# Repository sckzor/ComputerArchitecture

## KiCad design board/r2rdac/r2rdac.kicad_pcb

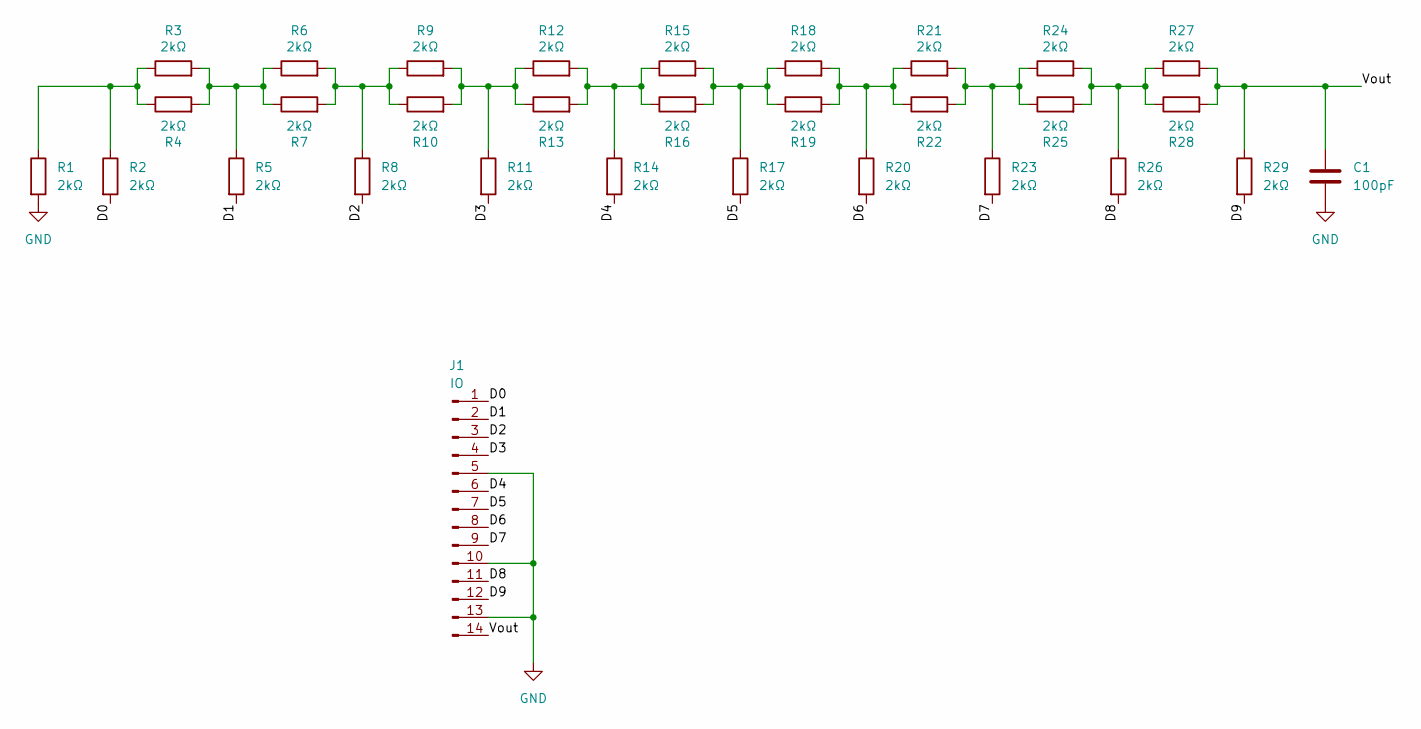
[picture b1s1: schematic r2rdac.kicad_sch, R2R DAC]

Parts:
C1: 100pF; C_0603_1608Metric
J1: IO; PinHeader_1x14_P2.54mm_Vertical
R1, R2, R3, R4, R5, R6, R7, R8, R9, R10, R11, R12, R13, R14, R15, R16, R17, R18, R19, R20, R21, R22, R23, R24, R25, R26, R27, R28, R29: 2kΩ; R_0603_1608Metric

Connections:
/D0: J1.1, R2.2
/D1: J1.2, R5.2
/D2: J1.3, R8.2
/D3: J1.4, R11.2
/D4: J1.6, R14.2
/D5: J1.7, R17.2
/D6: J1.8, R20.2
/D7: J1.9, R23.2
/D8: J1.11, R26.2
/D9: J1.12, R29.2
/Vout: C1.1, J1.14, R27.2, R28.2, R29.1
GND: C1.2, J1.5, J1.10, J1.13, R1.2
unnamed: R1.1, R2.1, R3.1, R4.1
unnamed: R3.2, R4.2, R5.1, R6.1, R7.1
unnamed: R6.2, R7.2, R8.1, R9.1, R10.1
unnamed: R9.2, R10.2, R11.1, R12.1, R13.1
unnamed: R12.2, R13.2, R14.1, R15.1, R16.1
unnamed: R15.2, R16.2, R17.1, R18.1, R19.1
unnamed: R18.2, R19.2, R20.1, R21.1, R22.1
unnamed: R21.2, R22.2, R23.1, R24.1, R25.1
unnamed: R24.2, R25.2, R26.1, R27.1, R28.1

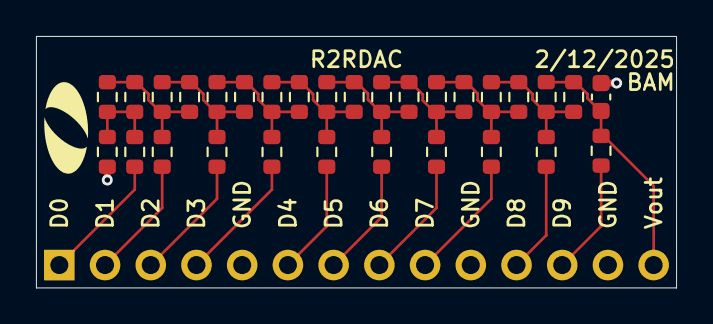
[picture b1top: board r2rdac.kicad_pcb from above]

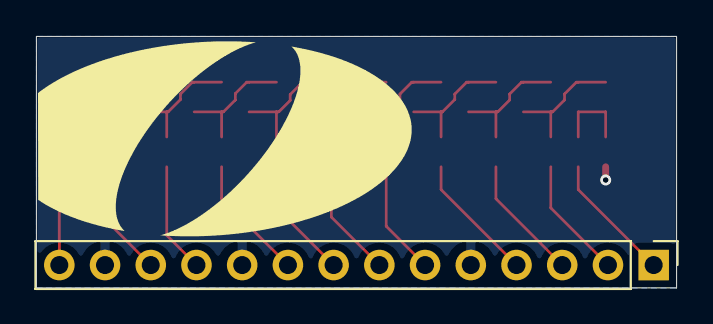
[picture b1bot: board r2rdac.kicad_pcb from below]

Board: 2 copper layers, 35.6 x 14.0 mm, 33 parts (2 on the bottom side), 21 nets.

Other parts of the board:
OlinLogoSm: G***; OlinLogoSm
svg2mod: G***; OlinLogoTruncated_0.4in

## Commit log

2025-09-22 Added all resources to the repository and my frist project assignment.
2025-09-22 Added video and changed file names
2025-09-30 Added all files for MP2
2025-09-30 added MP2 video
2025-10-03 Performed next code revision
2025-10-06 redid MP2
2025-10-13 wrote led driver
2025-10-13 added game of life logic
2025-10-15 finished most of game of life
2025-10-18 started adding cyclic boundary
2025-10-18 fixed small issues now
2025-10-18 missed a bit on the colors
2025-10-27 Added the preprocessor directives to do simulations
2025-10-27 added video
2025-10-27 removed extra file
2025-10-27 Added the write up
2025-10-27 Updated the Write-Up
2025-10-27 Fixed a typo in the writeup
2025-10-27 Updated the Write-Up Again
2025-10-27 Fixed an error in the python script
2025-11-11 Got things working in sim for the most part
2025-11-12 works but way too much resource usage when synthesized
2025-11-12 down to 108% utilization
2025-11-15 Passing all tests and synthesizes
2025-12-01 added demo video
2025-12-04 added most of final
2025-12-04 updated the code for the processor to fix a minor error
2025-12-14 added final project files
2025-12-14 added final demo video:
